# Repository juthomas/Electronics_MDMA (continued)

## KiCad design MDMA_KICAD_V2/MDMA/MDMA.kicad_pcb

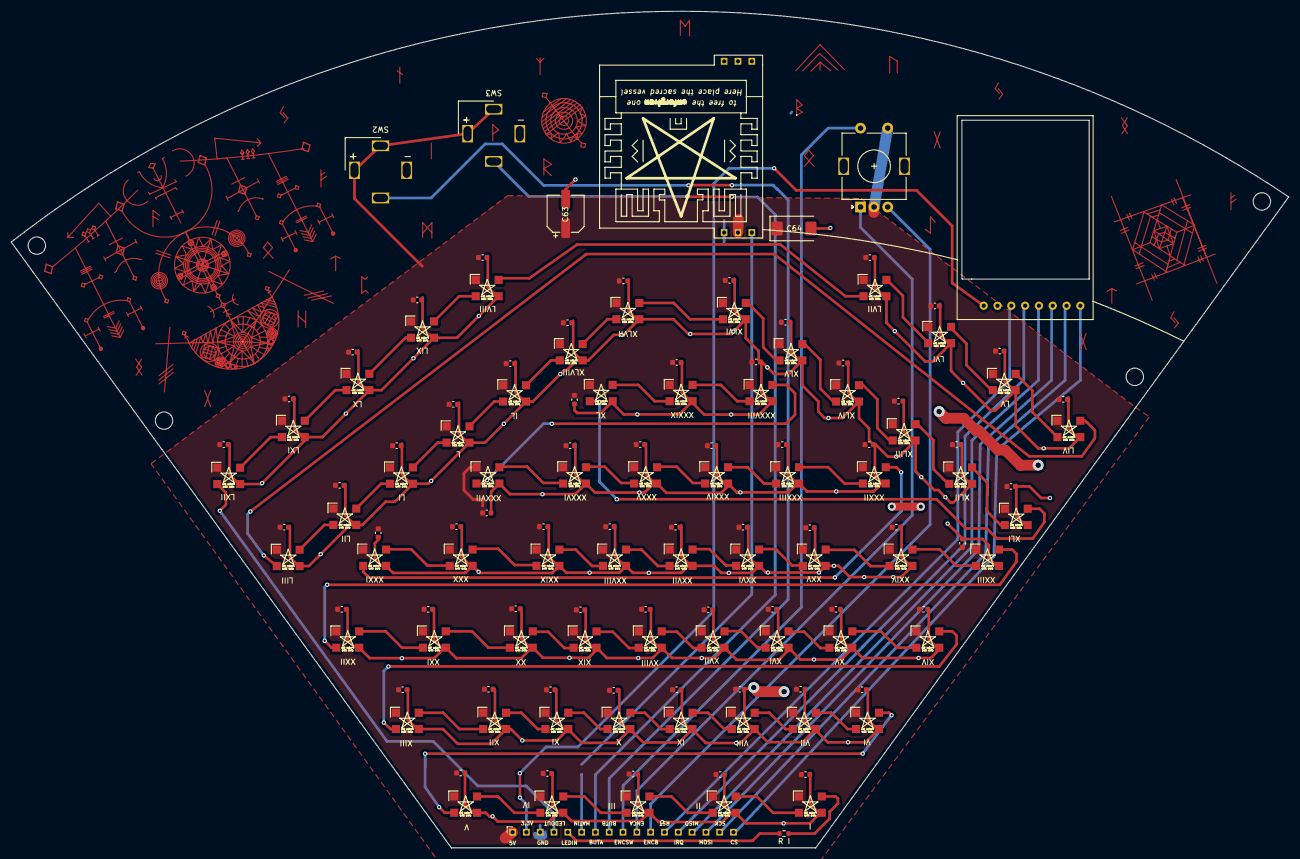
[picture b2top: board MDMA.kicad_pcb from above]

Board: 2 copper layers, 235.0 x 153.9 mm, 138 parts (1 on the bottom side), 80 nets.

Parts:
C1, C2, C3, C4, C5, C6, C7, C8, C9, C10, C11, C12, C13, C14, C15, C16, C17, C18, C19, C20, C21, C22, C23, C24, C25, C26, C27, C28, C29, C30, C31, C32, C33, C34, C35, C36, C37, C38, C39, C40, C41, C42, C43, C44, C45, C46, C47, C48, C49, C50, C51, C52, C53, C54, C55, C56, C57, C58, C59, C60, C61, C62: 100nF; C_0603_1608Metric
C63: 470uF; CP_Elec_6.3x7.7
C64: 470uf; CP_EIA-7343-30_AVX-N
H1, H2, H3, H4: MountingHole; MountingHole_3.2mm_M3
I: WS2812-2020; WS2812B
II: WS2812-2020; WS2812B
III: WS2812-2020; WS2812B
IL: WS2812-2020; WS2812B
IV: WS2812-2020; WS2812B
IX: WS2812-2020; WS2812B
L: WS2812-2020; WS2812B
LI: WS2812-2020; WS2812B
LII: WS2812-2020; WS2812B
LIII: WS2812-2020; WS2812B
LIV: WS2812-2020; WS2812B
LIX: WS2812-2020; WS2812B
LV: WS2812-2020; WS2812B
LVI: WS2812-2020; WS2812B
LVII: WS2812-2020; WS2812B
LVIII: WS2812-2020; WS2812B
LX: WS2812-2020; WS2812B
LXI: WS2812-2020; WS2812B
LXII: WS2812-2020; WS2812B
P1: Switch_Pin_out; Pizza_Pin_Out
R I: 300/0 Ohm; R_0603_1608Metric
R II: 300 Ohm; R_0603_1608Metric
SW1: Rotary_Encoder_Switch; RotaryEncoder_Alps_EC11E-Switch_Vertical_H20mm
SW2, SW3: SW_Push_LED; SW_LED_16mm
T1: RFID_Module; RFID_RC522
U1: Matrice8x8_WS2812
V: WS2812-2020; WS2812B
VI: WS2812-2020; WS2812B
VII: WS2812-2020; WS2812B
VIII: WS2812-2020; WS2812B
X: WS2812-2020; WS2812B
XI: WS2812-2020; WS2812B
XII: WS2812-2020; WS2812B
XIII: WS2812-2020; WS2812B
XIV: WS2812-2020; WS2812B
XIX: WS2812-2020; WS2812B
XL: WS2812-2020; WS2812B
XLI: WS2812-2020; WS2812B
XLII: WS2812-2020; WS2812B
XLIII: WS2812-2020; WS2812B
XLIV: WS2812-2020; WS2812B
XLV: WS2812-2020; WS2812B
XLVI: WS2812-2020; WS2812B
XLVII: WS2812-2020; WS2812B
XLVIII: WS2812-2020; WS2812B
XV: WS2812-2020; WS2812B
XVI: WS2812-2020; WS2812B
XVII: WS2812-2020; WS2812B
XVIII: WS2812-2020; WS2812B
XX: WS2812-2020; WS2812B
XXI: WS2812-2020; WS2812B
XXII: WS2812-2020; WS2812B
XXIII: WS2812-2020; WS2812B
XXIV: WS2812-2020; WS2812B
XXIX: WS2812-2020; WS2812B
XXV: WS2812-2020; WS2812B
XXVI: WS2812-2020; WS2812B
XXVII: WS2812-2020; WS2812B
XXVIII: WS2812-2020; WS2812B
XXX: WS2812-2020; WS2812B
XXXI: WS2812-2020; WS2812B
XXXII: WS2812-2020; WS2812B
XXXIII: WS2812-2020; WS2812B
XXXIV: WS2812-2020; WS2812B
XXXIX: WS2812-2020; WS2812B
XXXV: WS2812-2020; WS2812B
XXXVI: WS2812-2020; WS2812B
XXXVII: WS2812-2020; WS2812B
XXXVIII: WS2812-2020; WS2812B

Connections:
+3V3: P1.2, T1.1
+5V: C1.1, C2.1, C3.1, C4.1, C5.1, C6.1, C7.1, C8.1, C9.1, C10.1, C11.1, C12.1, C13.1, C14.1, C15.1, C16.1, C17.1, C18.1, C19.1, C20.1, C21.1, C22.1, C23.1, C24.1, C25.1, C26.1, C27.1, C28.1, C29.1, C30.1, C31.1, C32.1, C33.1, C34.1, C35.1, C36.1, C37.1, C38.1, C39.1, C40.1, C41.1, C42.1, C43.1, C44.1, C45.1, C46.1, C47.1, C48.1, C49.1, C50.1, C51.1, C52.1, C53.1, C54.1, C55.1, C56.1, C57.1, C58.1, C59.1, C60.1, C61.1, C62.1, C63.1, C64.1, I.1, II.1, III.1, IL.1, IV.1, IX.1, L.1, LI.1, LII.1, LIII.1, LIV.1, LIX.1, LV.1, LVI.1, LVII.1, LVIII.1, LX.1, LXI.1, LXII.1, P1.1, SW1.C, SW1.S1, SW2.1, SW2.4, SW3.1, SW3.4, U1.2, V.1, VI.1, VII.1, VIII.1, X.1, XI.1, XII.1, XIII.1, XIV.1, XIX.1, XL.1, XLI.1, XLII.1, XLIII.1, XLIV.1, XLV.1, XLVI.1, XLVII.1, XLVIII.1, XV.1, XVI.1, XVII.1, XVIII.1, XX.1, XXI.1, XXII.1, XXIII.1, XXIV.1, XXIX.1, XXV.1, XXVI.1, XXVII.1, XXVIII.1, XXX.1, XXXI.1, XXXII.1, XXXIII.1, XXXIV.1, XXXIX.1, XXXV.1, XXXVI.1, XXXVII.1, XXXVIII.1
/leds/DATA_IN: I.4, R I.1
/leds/DATA_OUT: LXII.2, P1.4
/leds/sheet5FFCCB65/DIN: I.2, II.4
/leds/sheet5FFCCCDC/DIN: II.2, III.4
/leds/sheet5FFCCEA1/DIN: III.2, IV.4
/leds/sheet5FFCD054/DIN: IV.2, V.4
/leds/sheet5FFCD56C/DIN: VI.2, VII.4
/leds/sheet5FFCD275/DIN: V.2, VI.4
/leds/sheet5FFCD801/DIN: VII.2, VIII.4
/leds/sheet5FFCE96D/DIN: IX.4, VIII.2
/leds/sheet5FFCE96E/DIN: IX.2, X.4
/leds/sheet5FFCE96F/DIN: X.2, XI.4
/leds/sheet5FFCE970/DIN: XI.2, XII.4
/leds/sheet5FFCE971/DIN: XII.2, XIII.4
/leds/sheet5FFCE972/DIN: XIII.2, XIV.4
/leds/sheet5FFCE973/DIN: XIV.2, XV.4
/leds/sheet5FFCE974/DIN: XV.2, XVI.4
/leds/sheet5FFCF15A/DIN: XVII.2, XVIII.4
/leds/sheet5FFCF15B/DIN: XIX.4, XVIII.2
/leds/sheet5FFCF15C/DIN: XIX.2, XX.4
/leds/sheet5FFCF15D/DIN: XX.2, XXI.4
/leds/sheet5FFCF15E/DIN: XXI.2, XXII.4
/leds/sheet5FFCF15F/DIN: XXII.2, XXIII.4
/leds/sheet5FFCF159/DIN: XVI.2, XVII.4
/leds/sheet5FFCF160/DIN: XXIII.2, XXIV.4
/leds/sheet5FFCFCC1/DIN: XXIV.2, XXV.4
/leds/sheet5FFCFCC2/DIN: XXV.2, XXVI.4
/leds/sheet5FFCFCC3/DIN: XXVI.2, XXVII.4
/leds/sheet5FFCFCC4/DIN: XXVII.2, XXVIII.4
/leds/sheet5FFCFCC5/DIN: XXIX.4, XXVIII.2
/leds/sheet5FFCFCC6/DIN: XXIX.2, XXX.4
/leds/sheet5FFCFCC7/DIN: XXX.2, XXXI.4
/leds/sheet5FFCFCC8/DIN: XXXI.2, XXXII.4
/leds/sheet5FFD0AB9/DIN: XXXII.2, XXXIII.4
/leds/sheet5FFD0ABA/DIN: XXXIII.2, XXXIV.4
/leds/sheet5FFD0ABB/DIN: XXXIV.2, XXXV.4
/leds/sheet5FFD0ABC/DIN: XXXV.2, XXXVI.4
/leds/sheet5FFD0ABD/DIN: XXXVI.2, XXXVII.4
/leds/sheet5FFD0ABE/DIN: XXXVII.2, XXXVIII.4
/leds/sheet5FFD0ABF/DIN: XXXIX.4, XXXVIII.2
/leds/sheet5FFD0AC0/DIN: XL.4, XXXIX.2
/leds/sheet5FFD1E5A/DIN: XLV.2, XLVI.4
/leds/sheet5FFD1E5B/DIN: XLVI.2, XLVII.4
/leds/sheet5FFD1E5C/DIN: XLVII.2, XLVIII.4
/leds/sheet5FFD1E55/DIN: XL.2, XLI.4
/leds/sheet5FFD1E56/DIN: XLI.2, XLII.4
/leds/sheet5FFD1E57/DIN: XLII.2, XLIII.4
/leds/sheet5FFD1E58/DIN: XLIII.2, XLIV.4
/leds/sheet5FFD1E59/DIN: XLIV.2, XLV.4
/leds/sheet5FFD364A/DIN: IL.2, L.4
/leds/sheet5FFD364B/DIN: L.2, LI.4
/leds/sheet5FFD364C/DIN: LI.2, LII.4
/leds/sheet5FFD364D/DIN: LII.2, LIII.4
/leds/sheet5FFD364E/DIN: LIII.2, LIV.4
/leds/sheet5FFD364F/DIN: LIV.2, LV.4
/leds/sheet5FFD558A/DIN: LVII.2, LVIII.4
/leds/sheet5FFD558B/DIN: LIX.4, LVIII.2
/leds/sheet5FFD558C/DIN: LIX.2, LX.4
/leds/sheet5FFD558D/DIN: LX.2, LXI.4
/leds/sheet5FFD558E/DIN: LXI.2, LXII.4
/leds/sheet5FFD3649/DIN: IL.4, XLVIII.2
/leds/sheet5FFD3650/DIN: LV.2, LVI.4
/leds/sheet5FFD5589/DIN: LVI.2, LVII.4
/switch_led2/SW_OUTPUT: P1.7, SW3.2
/switch_led/SW_OUTPUT: P1.8, SW2.2
GND: C1.2, C2.2, C3.2, C4.2, C5.2, C6.2, C7.2, C8.2, C9.2, C10.2, C11.2, C12.2, C13.2, C14.2, C15.2, C16.2, C17.2, C18.2, C19.2, C20.2, C21.2, C22.2, C23.2, C24.2, C25.2, C26.2, C27.2, C28.2, C29.2, C30.2, C31.2, C32.2, C33.2, C34.2, C35.2, C36.2, C37.2, C38.2, C39.2, C40.2, C41.2, C42.2, C43.2, C44.2, C45.2, C46.2, C47.2, C48.2, C49.2, C50.2, C51.2, C52.2, C53.2, C54.2, C55.2, C56.2, C57.2, C58.2, C59.2, C60.2, C61.2, C62.2, C63.2, C64.2, I.3, II.3, III.3, IL.3, IV.3, IX.3, L.3, LI.3, LII.3, LIII.3, LIV.3, LIX.3, LV.3, LVI.3, LVII.3, LVIII.3, LX.3, LXI.3, LXII.3, P1.3, SW2.3, SW3.3, T1.2, U1.3, V.3, VI.3, VII.3, VIII.3, X.3, XI.3, XII.3, XIII.3, XIV.3, XIX.3, XL.3, XLI.3, XLII.3, XLIII.3, XLIV.3, XLV.3, XLVI.3, XLVII.3, XLVIII.3, XV.3, XVI.3, XVII.3, XVIII.3, XX.3, XXI.3, XXII.3, XXIII.3, XXIV.3, XXIX.3, XXV.3, XXVI.3, XXVII.3, XXVIII.3, XXX.3, XXXI.3, XXXII.3, XXXIII.3, XXXIV.3, XXXIX.3, XXXV.3, XXXVI.3, XXXVII.3, XXXVIII.3
unnamed: P1.5, R I.2
unnamed: P1.6, R II.2
unnamed: P1.9, SW1.S2
unnamed: P1.10, SW1.A
unnamed: P1.11, SW1.B
unnamed: P1.12, T1.3
unnamed: P1.13, T1.4
unnamed: P1.14, T1.5
unnamed: P1.15, T1.6
unnamed: P1.16, T1.7
unnamed: P1.17, T1.8
unnamed: R II.1, U1.1

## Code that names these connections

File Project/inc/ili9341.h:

#ifndef ILI9341_H
# define ILI9341_H

# include <avr/interrupt.h>
# include <avr/io.h>
#include <avr/pgmspace.h>
#include <stdint.h>
#include "./ili9341command.h"
#include "./ili9341_font.h"

#define ILI9341_TFTWIDTH 240
#define ILI9341_TFTHEIGHT 320

#define TFT_DC 46
#define TFT_CS 53
#define TFT_RST 48
#define TFT_MOSI 51
#define TFT_CLK 52
#define TFT_MISO 50

//#ifndef _BV(bit)
// #define _BV(bit) (1<<(bit))
//#endif

#define AVR_WRITESPI(x) for (SPDR = (x); (!(SPSR & _BV(SPIF)));)
#define abs(x) ((x) < 0 ? -(x) : (x))
#define MIN(X, Y) (((X) < (Y)) ? (X) : (Y))
#define MAX(X, Y) (((X) > (Y)) ? (X) : (Y))
#define MISO_WRITE 37
#define _swap_int16_t(a, b) \
    {                       \
        int16_t t = a;      \
        a = b;              \
        b = t;              \
    }

// Color definitions, stollen like most of the actual code from adafruit lol
#define ILI9341_BLACK 0x0000       ///<   0,   0,   0
#define ILI9341_NAVY 0x000F        ///<   0,   0, 123
#define ILI9341_DARKGREEN 0x03E0   ///<   0, 125,   0
#define ILI9341_DARKCYAN 0x03EF    ///<   0, 125, 123
#define ILI9341_MAROON 0x7800      ///< 123,   0,   0
#define ILI9341_PURPLE 0x780F      ///< 123,   0, 123
#define ILI9341_OLIVE 0x7BE0       ///< 123, 125,   0
#define ILI9341_LIGHTGREY 0xC618   ///< 198, 195, 198
#define ILI9341_DARKGREY 0x7BEF    ///< 123, 125, 123
#define ILI9341_BLUE 0x001F        ///<   0,   0, 255
#define ILI9341_GREEN 0x07E0       ///<   0, 255,   0
#define ILI9341_CYAN 0x07FF        ///<   0, 255, 255
#define ILI9341_RED 0xF800         ///< 255,   0,   0
#define ILI9341_MAGENTA 0xF81F     ///< 255,   0, 255
#define ILI9341_YELLOW 0xFFE0      ///< 255, 255,   0
#define ILI9341_WHITE 0xFFFF       ///< 255, 255, 255
#define ILI9341_ORANGE 0xFD20      ///< 255, 165,   0
#define ILI9341_GREENYELLOW 0xAFE5 ///< 173, 255,  41
#define ILI9341_PINK 0xFC18

#define _swap_int16_t(a, b) \
    {                       \
        int16_t t = a;      \
        a = b;              \
        b = t;              \
    }

typedef uint32_t ADAGFX_PORT_t;
typedef volatile ADAGFX_PORT_t *PORTreg_t;

volatile uint8_t *portSPI;
volatile uint8_t *portPINL;

uint8_t spcr;
uint8_t spsr;

int16_t cursor_x;
int16_t cursor_y;
uint16_t textcolor;
uint16_t textbgcolor;
uint8_t textsize_x;   ///< Desired magnification in X-axis of text to print()
uint8_t textsize_y;
uint8_t cp437;
uint8_t wrap;

uint8_t rotation;

int16_t width;       ///< Display width as modified by current rotation
int16_t height;


void    ili9341_begin(void);
void    ili9341_fillRect(int16_t x, int16_t y, int16_t w, int16_t h, uint16_t color, uint8_t delay);
void    spiWrite(uint8_t b);
void    ili9341_setCursor(int16_t x, int16_t y);
void    ili9341_setTextColor(uint16_t c);
void    ili9341_setTextSize(uint8_t s);
void    write(uint8_t c, int16_t color, uint8_t size, uint8_t delay, int16_t startX, int16_t endX);
void    ili9341_println(char *str, int16_t color, uint8_t size, uint8_t delay);
void    ili9341_print(char *str, int16_t color, uint8_t size, uint8_t delay, int16_t startX, int16_t endX);
void    setAddrWindow(uint16_t x1, uint16_t y1, uint16_t w, uint16_t h, uint8_t delay);
void    SPI_WRITE16(uint16_t w, uint8_t delay);
void    ili9341_setRotation(uint8_t m);
void    ili9341_fillScreen(uint16_t color);
void    writePixel(int16_t x, int16_t y, uint16_t color, uint8_t delay);
void    ili9341_drawLine(uint16_t x1, uint16_t y1, uint16_t x2, uint16_t y2, uint16_t color, uint8_t delay);
void    spi_begin_transaction(void);
void    spi_end_transaction(void);
void    ili9341_drawfillCircle(int16_t x0, int16_t y0, int16_t r, uint16_t color, uint8_t delay);
void    writeLine(int16_t x0, int16_t y0, int16_t x1, int16_t y1, uint16_t color, uint8_t delay);
void    ili9341_drawfillRect(int16_t x, int16_t y, int16_t w, int16_t h, uint16_t color, uint8_t delay);
void    ili9341_drawRect(int16_t x, int16_t y, int16_t w, int16_t h, uint16_t color);
uint16_t color565(uint8_t red, uint8_t green, uint8_t blue);
void    graphic_test(void);
void	ili9341_putnbr(int8_t n, int16_t color, uint8_t size, uint8_t delay);
void	ili9341_putnbrln(int8_t n, int16_t color, uint8_t size, uint8_t delay);

void    ili9341_draw_IMG(const uint8_t *bitmap, const uint16_t *palette, int16_t x, int16_t y, int16_t width, int16_t height, int16_t scale);
void    writeColor(uint16_t color, uint32_t len, uint8_t delay);
void    ili9341_putnbr_base(int32_t nbr, char *base, int16_t color, uint8_t size, uint8_t delay);
void    ili9341_putnbr_baseln(int32_t nbr, char *base, int16_t color, uint8_t size, uint8_t delay);
#endif

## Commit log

2021-02-08 [ADD] Base atmega2560
2021-02-09 [ADD] debug rule
2021-02-11 [ADD] pinout imgs
2021-02-11 [ADD] beg assembly, but how to write PORTB ?
2021-02-12 [ADD] registers works (but strange behaviour)
2021-02-12 [ADD] strange behaviour comments
2021-02-12 [ADD] multi pins testing
2021-02-22 [ADD] some changes
2021-02-22 [ADD] makefile multifiles
2021-02-22 [ADD] idk
2021-02-22 [ADD] makefile care of includes
2021-02-22 [ADD] make help + phony
2021-02-22 [ADD] mute > unmute
2021-02-22 [ADD] new makefile on WS2812
2021-02-22 [RM] blank project
2021-02-22 [ADD] beg pin registers
2021-02-22 [ADD] header
2021-02-22 [ADD] needs test
2021-02-23 [UPD] reverse pin direction
2021-02-23 [ADD] tests for pin manipulation
2021-02-23 [UPD] fix digital read
2021-02-23 [ADD] template new file makefile
2021-02-23 [ADD] explicit Low=0
2021-02-23 [CLEAN] rm things for branching
2021-02-23 [ADD] Readme
2021-02-23 [UPDT] Readme
2021-02-23 IT DRAW SOMETHING
2021-02-23 [ADD] spacing
2021-02-23 [ADD] fix spacing
2021-02-23 [ADD] spacing and more
2021-02-23 [ADD] avr-gcc install macos
2021-02-23 [ADD] Linter
2021-02-23 [ADD] "folder" word
2021-02-23 [UPDT] Title
2021-02-23 [UPDT] upper case img folder
2021-02-23 [ADD] summary
2021-02-23 [ADD] summary changes
2021-02-23 [ADD] brew installation
2021-02-23 [ADD] colons
2021-02-23 [ADD] space
2021-02-23 [ADD] dot h
2021-02-23 [ADD] avr dude installation
2021-02-23 [ADD] test badge
2021-02-23 [ADD] badges test
2021-02-23 [ADD] test bagdes
2021-02-23 [ADD] tests badges
2021-02-23 [ADD] some badges
2021-02-23 [ADD] custom badge
2021-02-23 [ADD] More spacing
2021-02-23 [ADD] Spacing test
2021-02-23 [ADD] Spacing tests
2021-02-23 [ADD] tests spacings/badges
2021-02-23 [ADD] Badge size
2021-02-23 [ADD] debug img
2021-02-23 FASTER
2021-02-23 test
2021-02-23 [ADD] macos default avr path
2021-02-23 [ADD] \n
2021-02-23 [UPDT] description
2021-02-23 [UPDT] micro updt
2021-02-23 [UPDT] normed
2021-02-24 [ADD] beg leds part
2021-02-24 [ADD] main cleaned
2021-02-24 [ADD] serial debug
2021-02-24 Text in progress
2021-02-24 [ADD] labelec intellisense
2021-02-24 [ADD] avr word
2021-02-24 [ADD] normed
2021-02-24 Text Added
2021-02-24 before restarting after merge fail
2021-02-24 first after merge
2021-02-25 [ADD] atmega2560 board change
2021-02-25 reader first steps
2021-02-25 set_rotation
2021-02-25 starting read
2021-02-25 saved
2021-02-26 [ADD] didnt work yet
2021-02-26 add some comments from datasheet
2021-02-26 [ADD] leds flashing + beg music
2021-02-26 debug card check
2021-02-26 [RM] space
2021-03-01 lundi
2021-03-03 [ADD] bancal mais fait des trucs
2021-03-03 [ADD] some cancer code
2021-03-03 [ADD] Leds work
2021-03-04 [ADD] some things
2021-03-04 premier test de multiple bouton
2021-03-04 [ADD] Serial nbr base
2021-03-04 [ADD] 88 leds poc
2021-03-05 [ADD] Can select led pins (PORT >= H not yet here)
2021-03-05 [ADD] Leds works (not PORT > H)
2021-03-05 [ADD] Readme time
2021-03-05 [ADD] some testes
2021-03-05 [ADD] Functionalities part
2021-03-05 [ADD] aligned
2021-03-05 [ADD] Prerequisites
2021-03-05 [ADD] Some lignes for leds
2021-03-07 ILI9341 with Redbull
2021-03-08 [ADD] matrix works
2021-03-08 [ADD] Draw items
2021-03-08 [ADD] Precompiller for matrix items
2021-03-08 Can Read Imgs
2021-03-08 [ADD] Somes pixels art
2021-03-09 [ADD] dice + minecraft
2021-03-09 [ADD] items Colorization
2021-03-09 [ADD] Draw Line function
2021-03-11 homarie si tu savais
2021-03-15 tentative d interupte foireuse
2021-03-17 blabla
2021-03-18 [ADD] Can now play music !
2021-03-18 [ADD] Thats... probably... works...
2021-03-18 [ADD] Need to debug
2021-03-19 [ADD] Thats Works, but not clean
2021-03-19 [ADD] Matrice + music works !
2021-03-19 Button POC
2021-03-19 Little modifications
2021-03-19 migration arduino -> avr
2021-03-19 more clear
2021-03-19 changed dir
2021-03-19 [ADD] square and circle matrix drawing
2021-03-22 [UPD] PROGMEM .C -> .H
2021-03-22 [ADD] reduce .data + no warnings
2021-03-22 Merged done
2021-03-22 version interupt as deux bouton
2021-03-22 premier jet as 5
2021-03-22 5 qui marche
2021-03-22 [ADD] Poc fini
2021-03-23 All Merged together
2021-03-23 sa marche maboi
2021-05-10 laisse moi
2021-05-10 j ai besoin d un timer
2021-05-11 code mistique
2021-05-13 [ADD] Matrix sync
2021-05-13 [RM] Pin manipulation (Ram usage 84=>8%)
2021-05-13 [FIX] RAM USAGE
2021-05-13 [ADD] Lines between players
2021-05-14 [ADD] Interactions betweens players
2021-05-14 [ADD] Full interactions between players
2021-05-14 [ADD] Wawes interactions
2021-05-14 Intro in progress
2021-05-14 [ADD] Keep background after user interactions
2021-05-16 c est bon j ai virer le bazard
2021-05-16 matric de bouton fonctionelle ;)
2021-05-16 bouton pret as l emplois
2021-05-17 [TO FIX] regarde
2021-05-17 [ADD] Map funct + beg of circle pit
2021-05-17 More pixelarts
2021-05-17 [ADD] Circle pit done
2021-05-17 [ADD] Circle pit spin modes
2021-05-18 [BEG] Autolink_images
2021-05-18 [ADD] Auto-update matrix progmem
2021-05-18 Image Converter
2021-05-18 [ADD] Makefile can change matrix settings
2021-05-18 New Images + Converter IMG => Indexed in Gimp to 16 and export as .c, convert to .h and delete const.
2021-05-18 Image Folder
2021-05-18 Move The Folder Image in the right place
2021-05-18 [ADD] updt
2021-05-19 [BEG] Interactions with screen
2021-05-28 faut que je teste le code plus loin avr-gcc est pas dispo ici
2021-05-31 [FIX] New order or pizza parts
2021-05-31 New Images - Cadre Text
2021-05-31 [ADD] Comments
2021-05-31 Kicad shematics added
2021-06-02 First step of rangement
2021-06-02 More Data Space Work in progress
2021-06-02 Close to 60% Data. Don't know how to reduce
2021-06-02 [ADD] Buttons part
2021-06-02 [RM] Objects
2021-06-03 [ADD] Game Intro
2021-06-03 More Menus
2021-06-03 [ADD] Encoders Parts
2021-06-03 [MRG] Screen Animations
2021-06-03 [BEG] Encoders + Millis
2021-06-04 New images and games
2021-06-04 [FIX] Led matrix + Spi
2021-06-04 Begining of code cleaning, review of the code necessary/ Game Menu cleaner.
2021-06-04 [ADD] Numbers on matrix, but encoders bugs
2021-06-04 [ADD] Demo numbers
2021-06-05 Nothing to see here
2021-06-05 Merging
2021-06-05 SPI Working like hell <3
2021-06-07 Games implementation in progress
2021-06-07 [ADD] pin tmp
2021-06-07 stash
2021-06-07 [ADD] port history
2021-06-07 [ADD] Encoders seems Ok
2021-06-07 [UPDT] Clear buffer
2021-06-07 Rolling Dice
2021-06-07 New Image
2021-06-07 [ADD] millis
2021-06-07 [ADD] draw timer state (game)
2021-06-07 [FIX] for
2021-06-07 [ADD] Prepare bomb explosion
2021-06-07 Need Test / Save
2021-06-08 [ADD] New pixels arts
2021-06-08 Broken Games - 4 and 24hours
2021-06-08 Little addon
2021-06-08 [ADD] New arts in code
2021-06-09 [UPDT] Gun reversed
2021-06-09 [UPDT] Remove static prefix
2021-06-09 [ADD] Buttons Ticks + Pushed
2021-06-09 [UPDT] Halo
2021-06-09 [UPDT] Rm static
2021-06-09 [FIX] Buttons is clicking
2021-06-09 [FIX] Invert bitwise on is activate
2021-06-09 [ADD] Some pixels arts 8*8
2021-06-09 [ADD] Megalovania
2021-06-09 Project on Cocaine
2021-06-09 [UPDT] gimp pixel art
2021-06-09 [ADD] "Pong animation" (between players) and draw_timer_state
2021-06-09 [ADD] Rock paper scissors
2021-06-09 [ADD] Car note, double note
2021-06-09 [RE] Old pixel arts
2021-06-09 NEW GAME + ANIMATION + IT WORKSSSSSS
2021-06-09 [ADD] Ammo amount
2021-06-09 Little cherry
2021-06-10 [ADD] New rock
2021-06-10 [FIX] RPC and Cheers
2021-06-10 [RM] Useless things
2021-06-10 [ADD] Finals touchs
2021-06-10 [FIX] Press button to skip rules
2021-06-10 [UPDT] Waiting time for game name and game rules
2021-06-10 done
2021-06-10 last last
2021-07-08 Demo V1
2021-07-08 Demo V2
